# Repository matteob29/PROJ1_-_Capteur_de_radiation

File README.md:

# PROJ1 – Conception d’un capteur de radiation avec tube Geiger

Projet réalisé dans le cadre du module **PROJ1 – Projet analogique** en première année à l’**ENSEIRB-MATMECA**.

**Auteurs :** 

Mattéo BINET  
Quentin MARIE  

**Date :** 30 décembre 2025  

---

## 1. Introduction

Le projet de conception électronique consiste en l'étude et la réalisation d'un capteur de radiation fonctionnel et compact. Ce système repose sur l'utilisation d'un tube Geiger-Müller J315 pour la détection de particules ionisantes.

L'architecture du circuit est une adaptation modernisée du module CAJOE, transposée en technologie de composants montés en surface (CMS) afin de réduire l'encombrement global. La conception a été intégralement réalisée sous le logiciel de CAO **KiCad E.D.A. 9.0.5**.

---

## 2. Cahier des charges (Tube J315)

- **Type de tube :** Halogène à impulsion pour rayonnements beta et gamma.
- **Tension de travail recommandée :** 380 V.
- **Plage du plateau :** 80 V avec une pente maximale de 10 % / 80 V.
- **Tension d'alimentation :** +5 V DC.
- **Protection :** Fusible de 750 mA intégré pour prévenir les courts-circuits.
- **Consommation nominale :** Environ 40 mA.

---

## 3. Conception du circuit

Le circuit est divisé en quatre blocs fonctionnels principaux :

1. **Module d'Alimentation :**
   - Entrée via connecteur JST XH à trois broches (GND, INT, +5 V).
   - Protection par fusible F1 et filtrage par condensateur de découplage C1 (100 nF).
   - Interrupteur bipolaire SW1 pour la mise hors tension complète.

2. **Étage Boost DC-DC :**
   - Oscillateur basé sur un circuit intégré **NE555** (U1) configuré en mode astable.
   - Élévation de tension par découpage via une inductance L2 (10 mH) et un transistor haute tension **MMBTA42** (Q1).
   - Fréquence d'oscillation fixée à 7059 Hz.

3. **Tripleur de tension :**
   - Structure de type Cockcroft-Walton composée de trois diodes **ES1J** (D2, D3, D4) et de condensateurs haute tension (10 nF / 1000 V).
   - Permet d'atteindre la tension de polarisation théorique de 400 V par effet de pompe de charge.

4. **Détecteur d’impulsion :**
   - Le tube V1 génère une avalanche électronique lors du passage d'une particule.
   - Mise en forme du signal par un second **NE555** (U2) configuré en monostable pour produire une impulsion calibrée de 517 us.
   - Signalisation visuelle par une LED rouge D5 à chaque détection.

---

## 4. Résultats expérimentaux

Les mesures effectuées à l'oscilloscope valident le comportement théorique :

- **Sortie Boost :** Observation de pics de tension d'environ 280 V au nœud boost_dc.
- **Sortie Multiplicateur :** Stabilisation de la haute tension après l'étage de filtrage.
- **Plage de réglage :** Tension de sortie ajustable entre 200 V et 550 V via le potentiomètre RV1, permettant un calage précis à 380 V.

---

## 5. Procédure de réglage

Le réglage de la haute tension s'effectue impérativement sans le tube Geiger :

1. **Mise sous tension :** Alimenter la carte en +5 V et vérifier l'allumage de la LED verte D1.
2. **Mesure :** Placer un voltmètre (calibre 1000 V) entre le point de test "tripleur" et la masse.
3. **Ajustement :** Régler RV1 jusqu'à obtenir 380 V.
4. **Alternative :** Une mesure indirecte est possible au point de test TP_Geiger situé après un pont diviseur de 50 MOhm.

---

## 6. Conclusion

Ce projet a permis de valider la conception d'un compteur Geiger CMS performant. L'intégration des étages de puissance et de détection sur un PCB compact répond aux exigences de fiabilité et de sécurité fixées initialement. Le dispositif constitue une base documentée pour toute application de surveillance radiologique.

---

## 7. Contenu du dépôt GitHub

Le dépôt contient l'intégralité des fichiers nécessaires à la reproduction du projet :

- [Carte_électronique/](./Carte_électronique) -> Schématics, fichiers de routage PCB et modèles 3D Kicad
- [Composants/](./Composants) -> Lien des sites utiles
- [Datasheet/](./Datasheet) -> Fiches techniques des composants critiques (NE555, MMBTA42, J315)
- [code_J315/](./code_J315) -> Exemple de code Arduino pour le comptage des impulsions (PPS)
- [README.md](./README.md) -> Présentation du projet

---

© 2025 — Mattéo BINET, Quentin MARIE
Département Électronique — PROJ1
Enseirb-Matmeca — Capteur de rayonnement beta & gamma

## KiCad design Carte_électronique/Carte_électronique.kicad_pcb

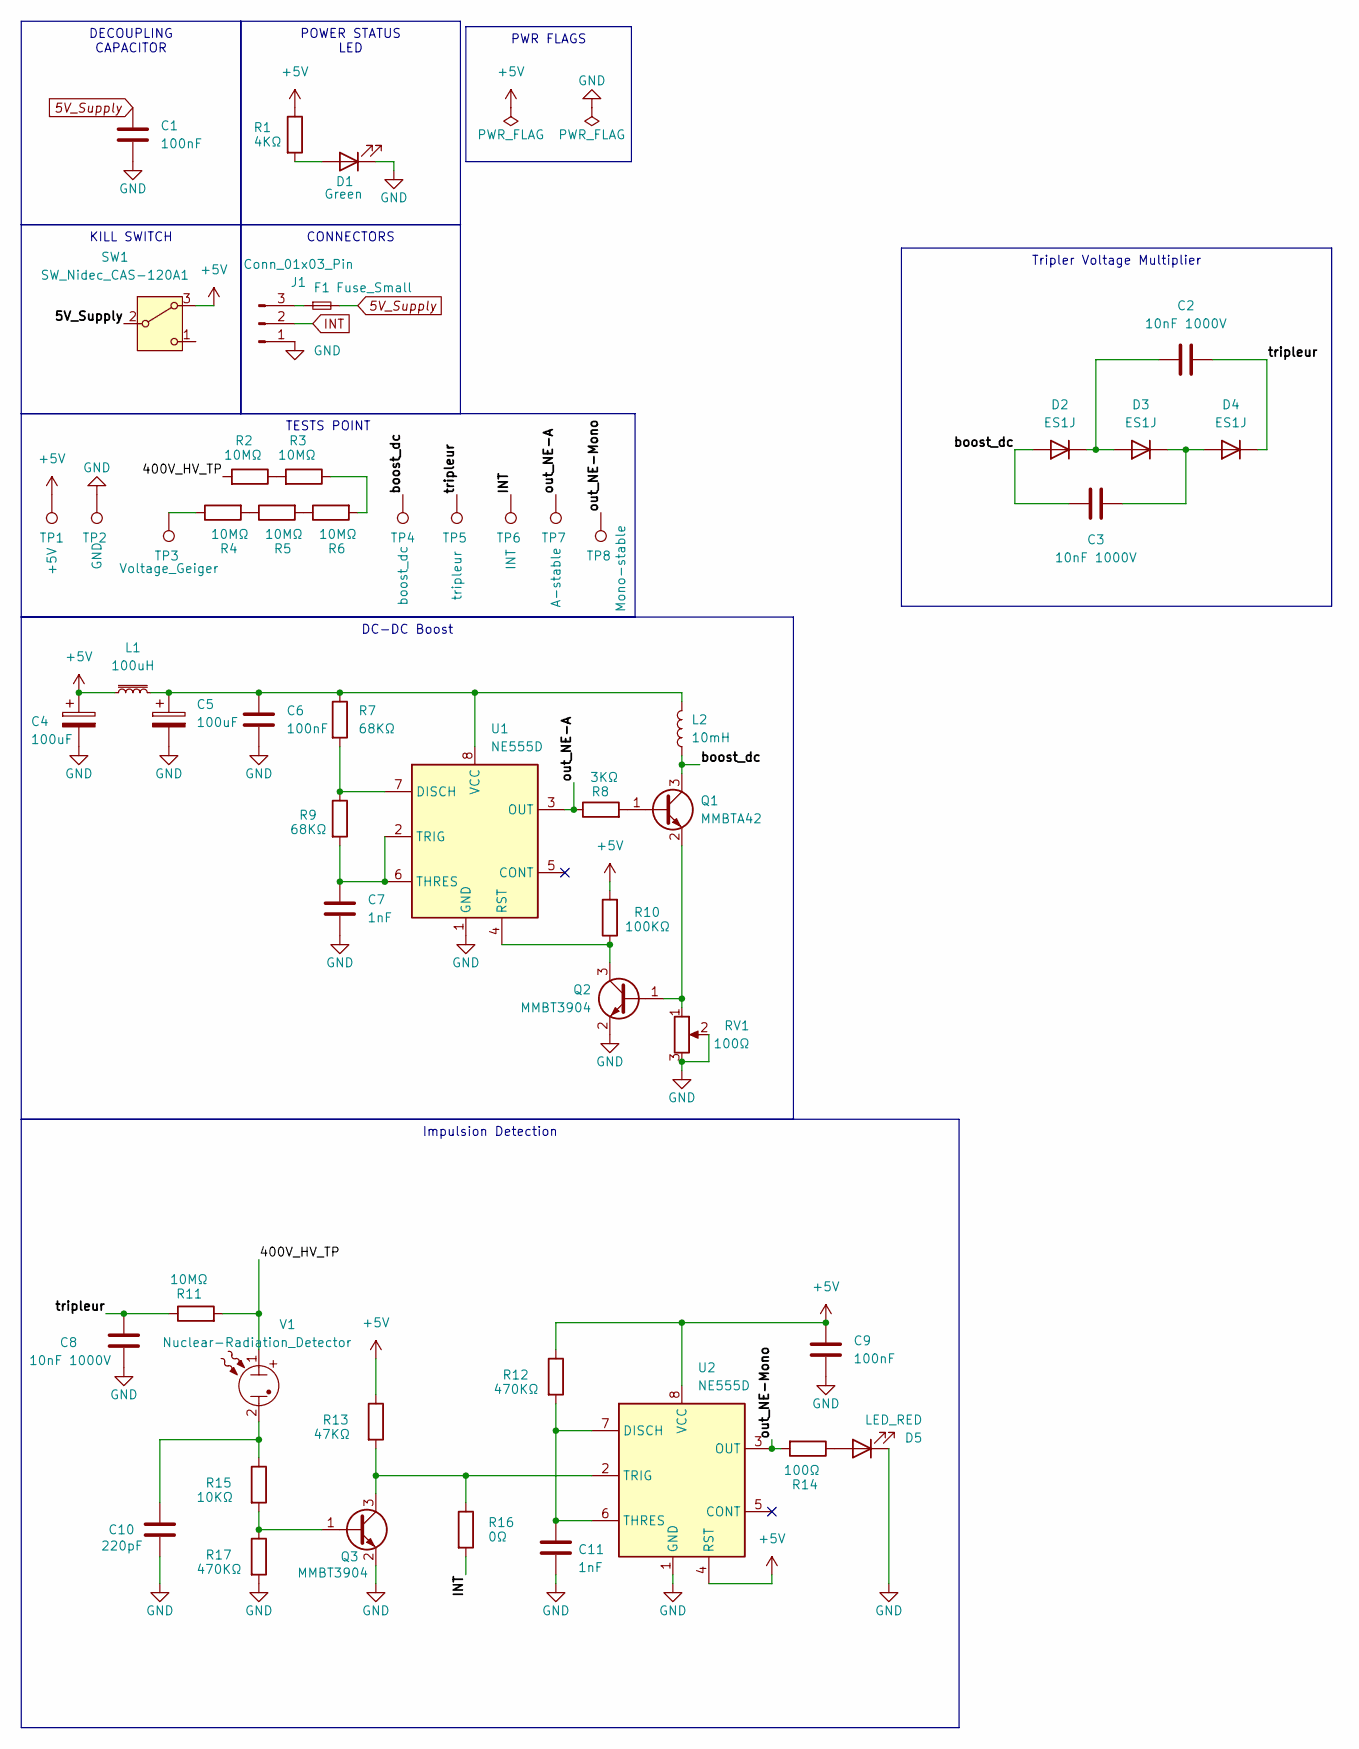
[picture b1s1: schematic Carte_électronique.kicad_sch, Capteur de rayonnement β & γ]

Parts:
C1, C6, C9: 100nF; C_0805_2012Metric_Pad1.18x1.45mm_HandSolder
C2, C3, C8: 10nF 1000V; C_1206_3216Metric_Pad1.33x1.80mm_HandSolder
C4, C5: 100uF; CP_Elec_5x5.3; Manufacturer PN UWT0J102MNL1GS; LCSC C445083
C7, C11: 1nF; C_0805_2012Metric_Pad1.18x1.45mm_HandSolder
C10: 220pF; C_0805_2012Metric_Pad1.18x1.45mm_HandSolder
D1: Green; LED_0805_2012Metric_Pad1.15x1.40mm_HandSolder; Manufacturer PN 151031VS06000
D2, D3, D4: ES1J; D_SMAF
D5: LED_RED; LED_0805_2012Metric_Pad1.15x1.40mm_HandSolder
F1: Fuse_Small; Fuse_0805_2012Metric_Pad1.15x1.40mm_HandSolder
J1: Conn_01x03_Pin; JST_XH_B3B-XH-A_1x03_P2.50mm_Vertical
L1: 100uH; L_Bourns_SRP7028A_7.3x6.6mm
L2: 10mH; L_Radial_D7.2mm_P3.00mm_Murata_1700
Q1: MMBTA42; D_SOT-23
Q2, Q3: MMBT3904; D_SOT-23
R1: 4KΩ; R_0805_2012Metric_Pad1.20x1.40mm_HandSolder; Manufacturer PN 0603WAF4700T5E; LCSC C23179
R2, R3, R4, R5, R6, R11: 10MΩ; R_0805_2012Metric_Pad1.20x1.40mm_HandSolder
R7, R9: 68KΩ; R_0805_2012Metric_Pad1.20x1.40mm_HandSolder
R8: 3KΩ; R_0805_2012Metric_Pad1.20x1.40mm_HandSolder
R10: 100KΩ; R_0805_2012Metric_Pad1.20x1.40mm_HandSolder
R12, R17: 470KΩ; R_0805_2012Metric_Pad1.20x1.40mm_HandSolder
R13: 47KΩ; R_0805_2012Metric_Pad1.20x1.40mm_HandSolder
R14: 100Ω; R_0805_2012Metric_Pad1.20x1.40mm_HandSolder
R15: 10KΩ; R_0805_2012Metric_Pad1.20x1.40mm_HandSolder
R16: 0Ω; R_0805_2012Metric_Pad1.20x1.40mm_HandSolder
RV1: 100Ω; Potentiometer_Bourns_TC33X_Vertical
SW1: SW_Nidec_CAS-120A1; SW_SPDT_PCM12
TP1: +5V; TestPoint_THTPad_D1.5mm_Drill0.7mm
TP2: GND; TestPoint_THTPad_D1.5mm_Drill0.7mm
TP3: Voltage_Geiger; TestPoint_THTPad_D1.5mm_Drill0.7mm
TP4: boost_dc; TestPoint_THTPad_D1.5mm_Drill0.7mm
TP5: tripleur; TestPoint_THTPad_D1.5mm_Drill0.7mm
TP6: INT; TestPoint_THTPad_D1.5mm_Drill0.7mm
TP7: A-stable; TestPoint_THTPad_D1.5mm_Drill0.7mm
TP8: Mono-stable; TestPoint_THTPad_D1.5mm_Drill0.7mm
U1, U2: NE555D; SOIC-8_3.9x4.9mm_P1.27mm
V1: Nuclear-Radiation_Detector; Tube_Geiger_J305

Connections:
5V_Supply: C1.1, F1.2, SW1.2 (B)
+5V: C4.1, C9.1, L1.1, R1.1, R10.2, R12.1, R13.1, SW1.3 (A), TP1.1, U2.4 (RST), U2.8 (VCC)
/400V_HV_TP: R2.2, R11.2, V1.1
/boost_dc: C3.2, D2.2 (A), L2.1, Q1.3 (C), TP4.1
/out_NE-A: R8.1, TP7.1, U1.3 (OUT)
/out_NE-Mono: R14.2, TP8.1, U2.3 (OUT)
/tripleur: C2.2, C8.1, D4.1 (K), R11.1, TP5.1
GND: C1.2, C4.2, C5.2, C6.2, C7.2, C8.2, C9.2, C10.2, C11.2, D1.1 (K), D5.1 (K), J1.1, Q2.2 (E), Q3.2 (E), R17.2, RV1.2, RV1.3, TP2.1, U1.1 (GND), U2.1 (GND)
INT: J1.2, R16.2, TP6.1
unnamed: C10.1, R15.1, V1.2
unnamed: D1.2 (A), R1.2
unnamed: C2.1, D2.1 (K), D3.2 (A)
unnamed: C3.1, D3.1 (K), D4.2 (A)
unnamed: D5.2 (A), R14.1
unnamed: F1.1, J1.3
unnamed: Q1.1 (B), R8.2
unnamed: Q1.2 (E), Q2.1 (B), RV1.1
unnamed: Q2.3 (C), R10.1, U1.4 (RST)
unnamed: Q3.1 (B), R15.2, R17.1
unnamed: Q3.3 (C), R13.2, R16.1, U2.2 (TRIG)
unnamed: R2.1, R3.2
unnamed: R3.1, R6.2
unnamed: R4.1, TP3.1
unnamed: R4.2, R5.1
unnamed: R5.2, R6.1
unnamed: R7.2, R9.1, U1.7 (DISCH)
unnamed: C7.1, R9.2, U1.2 (TRIG), U1.6 (THRES)
unnamed: C5.1, C6.1, L1.2, L2.2, R7.1, U1.8 (VCC)
unnamed: C11.1, R12.2, U2.6 (THRES), U2.7 (DISCH)

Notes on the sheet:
Impulsion Detection
DC-DC Boost
KILL SWITCH
TESTS POINT
PWR FLAGS
Tripler Voltage Multiplier
DECOUPLING CAPACITOR
POWER STATUS LED
CONNECTORS

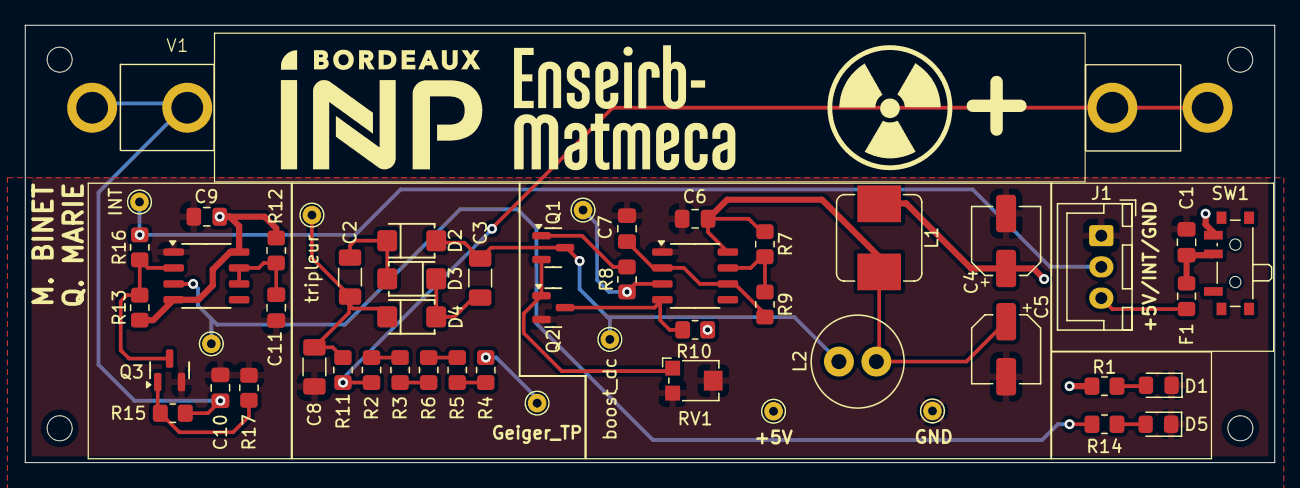
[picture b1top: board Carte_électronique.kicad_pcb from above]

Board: 2 copper layers, 100.0 x 35.0 mm, 53 parts (0 on the bottom side), 29 nets.

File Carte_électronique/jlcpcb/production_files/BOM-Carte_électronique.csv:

Comment,Designator,Footprint,LCSC,Quantity
220pF,C10,C_0805_2012Metric_Pad1.18x1.45mm_HandSolder,C107145,1
10MΩ,"R11,R2,R3,R4,R5,R6",R_0805_2012Metric_Pad1.20x1.40mm_HandSolder,C107700,6
SW_Nidec_CAS-120A1,SW1,SW_SPDT_PCM12,C109335,1
Conn_01x03_Pin,J1,JST_XH_B3B-XH-A_1x03_P2.50mm_Vertical,C144394,1
100Ω,R14,R_0805_2012Metric_Pad1.20x1.40mm_HandSolder,C17408,1
0Ω,R16,R_0805_2012Metric_Pad1.20x1.40mm_HandSolder,C17477,1
470KΩ,"R12,R17",R_0805_2012Metric_Pad1.20x1.40mm_HandSolder,C17709,2
47KΩ,R13,R_0805_2012Metric_Pad1.20x1.40mm_HandSolder,C17713,1
MMBTA42,Q1,D_SOT-23,C181172,1
4KΩ,R1,R_0805_2012Metric_Pad1.20x1.40mm_HandSolder,C23179,1
ES1J,"D2,D3,D4",D_SMAF,C232830,3
100uH,L1,L_Bourns_SRP7028A_7.3x6.6mm,C2894722,1
3KΩ,R8,R_0805_2012Metric_Pad1.20x1.40mm_HandSolder,C2907263,1
68KΩ,"R7,R9",R_0805_2012Metric_Pad1.20x1.40mm_HandSolder,C2933415,2
100uF,"C4,C5",CP_Elec_5x5.3,C445083,2
100nF,"C1,C6,C9",C_0805_2012Metric_Pad1.18x1.45mm_HandSolder,C49678,3
10mH,L2,L_Radial_D7.2mm_P3.00mm_Murata_1700,C5380230,1
NE555D,"U1,U2",SOIC-8_3.9x4.9mm_P1.27mm,C596355,2
Green,D1,LED_0805_2012Metric_Pad1.15x1.40mm_HandSolder,C84260,1
10KΩ,R15,R_0805_2012Metric_Pad1.20x1.40mm_HandSolder,C84376,1
Fuse_Small,F1,Fuse_0805_2012Metric_Pad1.15x1.40mm_HandSolder,C883111,1
100Ω,RV1,Potentiometer_Bourns_TC33X_Vertical,C911390,1
MMBT3904,"Q2,Q3",D_SOT-23,C916374,2
10nF 1000V,"C2,C3,C8",C_1206_3216Metric_Pad1.33x1.80mm_HandSolder,C9194,3
1nF,"C11,C7",C_0805_2012Metric_Pad1.18x1.45mm_HandSolder,C94121,2
100KΩ,R10,R_0805_2012Metric_Pad1.20x1.40mm_HandSolder,C96346,1
LED_RED,D5,LED_0805_2012Metric_Pad1.15x1.40mm_HandSolder,C965812,1

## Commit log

2025-12-30 Update authors and date in README
